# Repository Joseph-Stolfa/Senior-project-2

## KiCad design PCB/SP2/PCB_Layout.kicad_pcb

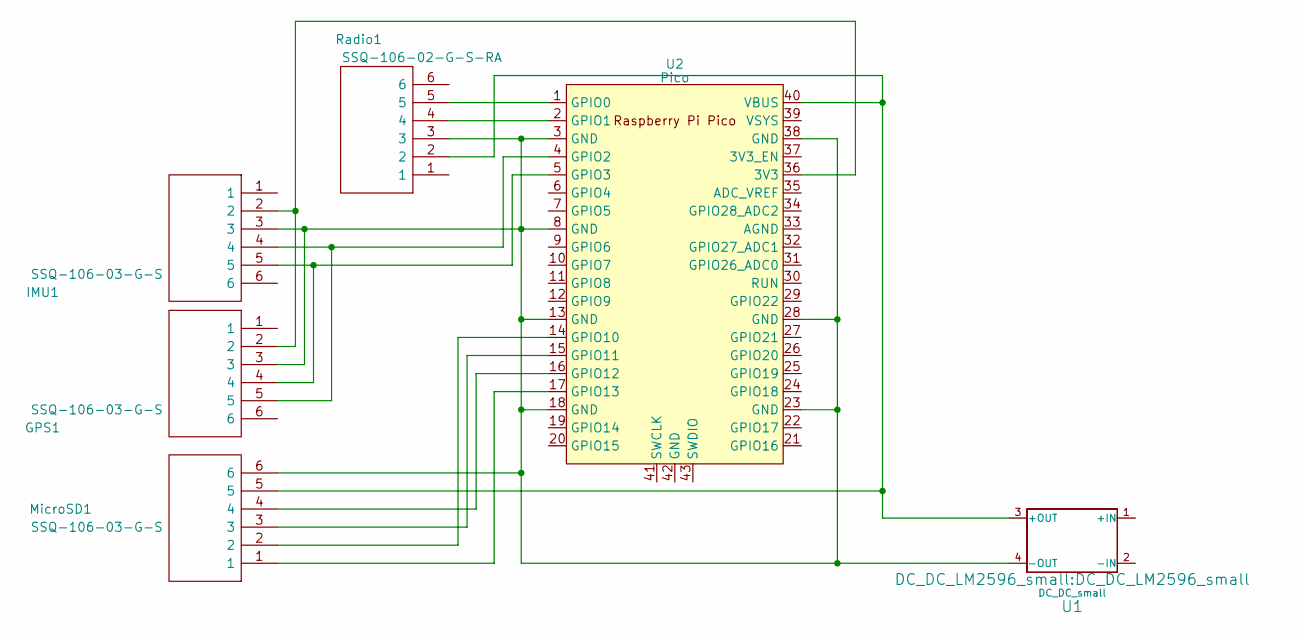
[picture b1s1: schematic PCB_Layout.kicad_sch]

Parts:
GPS1: SSQ-106-03-G-S; RHDR6W64P254_1X6_1575X241X851P; Mouser Part Number 200-SSQ10603GS
IMU1: SSQ-106-03-G-S; RHDR6W64P254_1X6_1575X241X851P; Mouser Part Number 200-SSQ10603GS
MicroSD1: SSQ-106-03-G-S; RHDR6W64P254_1X6_1575X241X851P; Mouser Part Number 200-SSQ10603GS
Radio1: SSQ-106-02-G-S-RA; RHDRRA6W64P254_1X6_1575X851X241P; Mouser Part Number 200-SSQ10602GSRA
U1: DC_DC_small; DC_DC_LM2596_small
U2: Pico; RPi_Pico_SMD_TH

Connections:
unnamed: MicroSD1.5, Radio1.2, U1.3 (+OUT), U2.40 (VBUS)
unnamed: GPS1.3, IMU1.3, MicroSD1.6, Radio1.3, U1.4 (-OUT), U2.3 (GND), U2.8 (GND), U2.13 (GND), U2.18 (GND), U2.23 (GND), U2.28 (GND), U2.38 (GND)
unnamed: GPS1.2, IMU1.2, U2.36 (3V3)
unnamed: Radio1.5, U2.1 (GPIO0)
unnamed: Radio1.4, U2.2 (GPIO1)
unnamed: GPS1.5, IMU1.4, U2.4 (GPIO2)
unnamed: GPS1.4, IMU1.5, U2.5 (GPIO3)
unnamed: MicroSD1.2, U2.14 (GPIO10)
unnamed: MicroSD1.3, U2.15 (GPIO11)
unnamed: MicroSD1.4, U2.16 (GPIO12)
unnamed: MicroSD1.1, U2.17 (GPIO13)

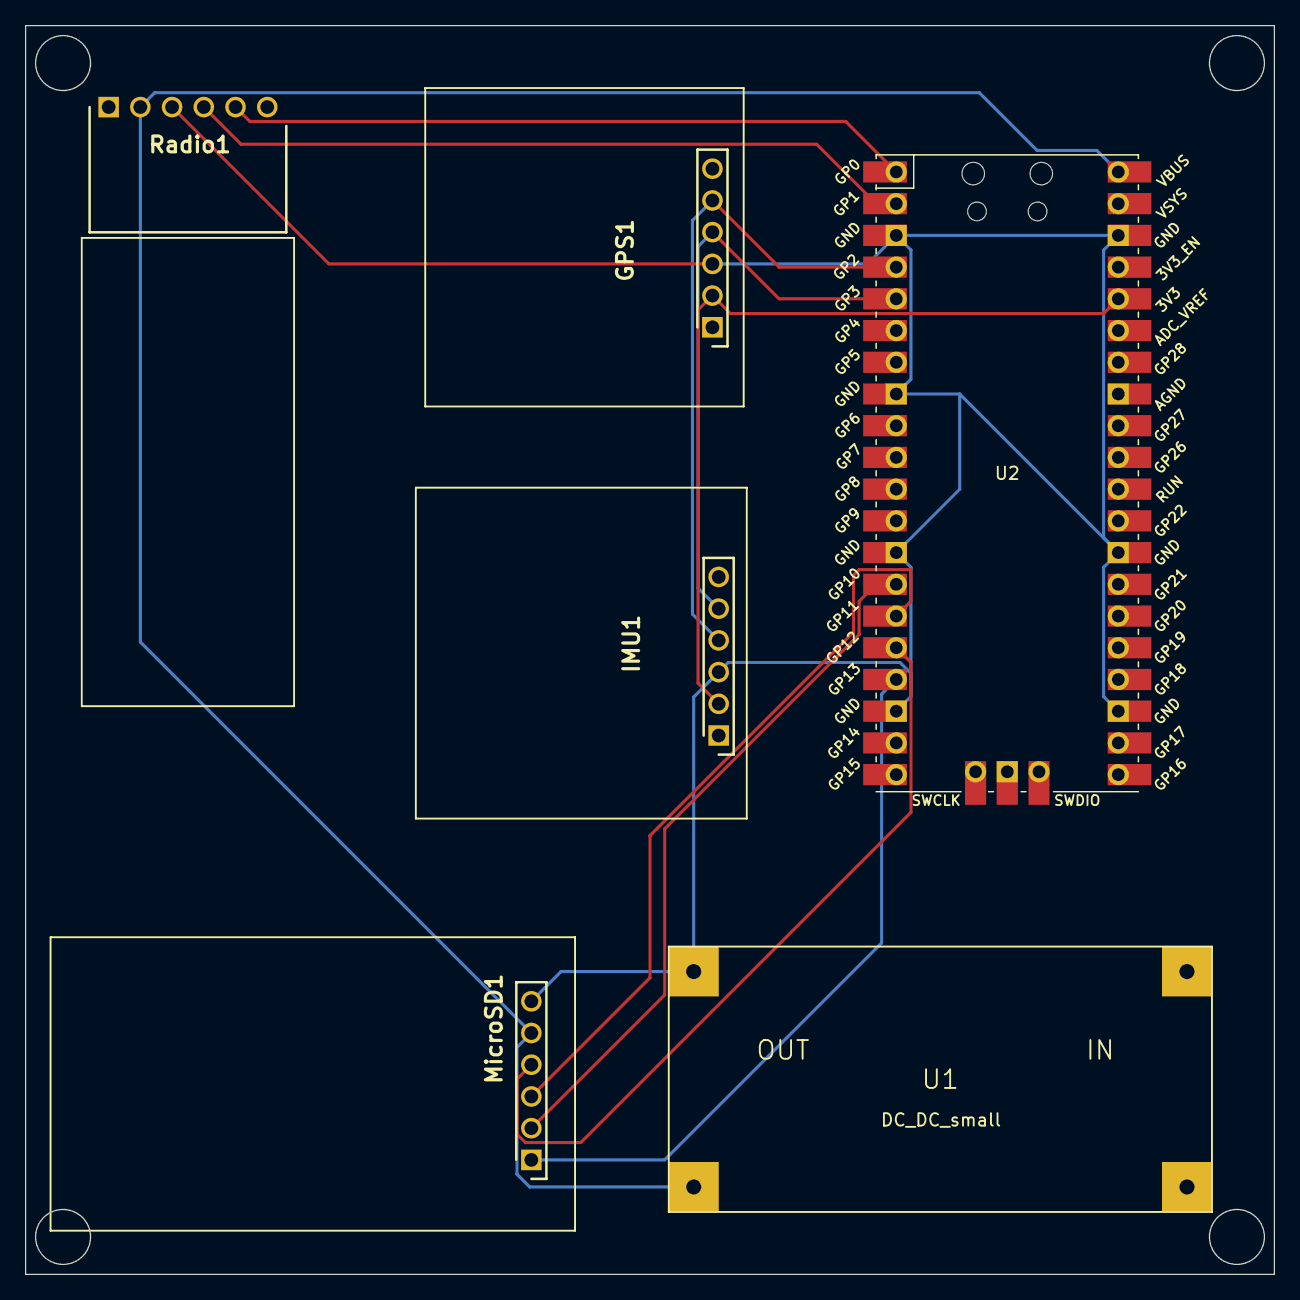
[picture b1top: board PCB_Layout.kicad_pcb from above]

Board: 2 copper layers, 100.0 x 100.0 mm, 6 parts (0 on the bottom side), 11 nets.

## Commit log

2023-04-03 Pcb info
2023-04-03 Pico code
2023-04-10 Added some code to the module I believe should work -UART alone has issues with multiple devices a mix of SPI, UART and I2C was implemented instead
2023-04-10 Added base kicad files
2023-04-10 added a I2C connection
2023-04-10 Update SP2.kicad_pcb
    Added the basic stuff i did
2023-04-10 Oops, wrong file
2023-04-10 Added the basic stuff i did
    Added it to the right file this time
2023-04-12 'Finished' Schematic
    Added the schematic, fully wired up
2023-04-17 Functional test code for the Pico for the following [IMU, GPS, Radio, USB]
    Additional work needs to be done in Pico's code to store information to SD and for 1 hour continuous use requirement
2023-04-17 Fixed Wires
    Cleaned up and fixed the schematic
2023-04-17 Added my files
    Added the files I use
2023-04-20 Updated PCB and Production files
2023-04-25 Code.py should have all functionality
